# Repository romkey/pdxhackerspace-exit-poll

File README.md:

# PDX Hackerspace Exit Poll

Exit Poll is a display next to the door that shows, from Home Assistant,
whether anything in the space needs attention before the last person
leaves: open doors, unlocked doors, running water and AV equipment left on.
At PDX Hackerspace the last person out checks the space's physical security
and turns off equipment; member Kenny M had the idea of putting a dashboard by
the door so departing members can see at a glance whether anything needs
doing. The repo also holds a sibling project, an appliance countdown display
(washer, dryer, dishwasher, oven, 3D printer), built from the same parts.

> **AI disclosure:** This project was written by AI under human oversight,
> following [these rules](https://github.com/romkey/esphome-ai-coding-rules/blob/main/RULES.md).

## What's here

| Path | What it is |
|------|------------|
| [`packages/exit-poll.yaml`](packages/exit-poll.yaml) | Reads the 16 per-section counts from Home Assistant, totals them and publishes a System Status (0 good … 4 urgent) |
| [`packages/exit-poll-leds.yaml`](packages/exit-poll-leds.yaml) | LED strip showing the status as a color, with switches and buttons to override it |
| [`packages/exit-poll-lcars-320x480.yaml`](packages/exit-poll-lcars-320x480.yaml) | LCARS-style screen for a 320x480 SPI panel (mipi_spi) |
| [`packages/exit-poll-lvgl-480x800.yaml`](packages/exit-poll-lvgl-480x800.yaml) | LCARS-style LVGL screen for a 480x800 (portrait) panel |
| [`packages/appliances.yaml`](packages/appliances.yaml) | Reads appliance remaining-time sensors from Home Assistant |
| [`packages/appliances-grid-480x320.yaml`](packages/appliances-grid-480x320.yaml) | 3x2 grid of five appliances plus a clock, 480x320 SPI panel |
| [`packages/appliances-2-line-480x320.yaml`](packages/appliances-2-line-480x320.yaml) | Clock plus washer and dryer in two large rows, 480x320 SPI panel |
| `packages/assets/` | Fonts and LCARS images the display packages use |
| [`examples/tinys3.yaml`](examples/tinys3.yaml) | Exit Poll on a TinyS3 (ESP32-S3) and the Exit Poll PCB, ILI9488 panel |
| [`examples/hosyond-4in-cyd.yaml`](examples/hosyond-4in-cyd.yaml) | Exit Poll on a Hosyond 4" ESP32 display (ESP32, ST7796) |
| [`examples/guition-8048s550.yaml`](examples/guition-8048s550.yaml) | Exit Poll on a Guition 5" ESP32-S3 display, LVGL |
| [`examples/tinypico-appliances.yaml`](examples/tinypico-appliances.yaml) | Appliance grid on a TinyPICO (ESP32) |
| [`examples/hosyond-4in-cyd-appliances.yaml`](examples/hosyond-4in-cyd-appliances.yaml) | Two-line appliance display on the Hosyond 4" board |
| `examples/common/` | Settings shared by all examples, and the Hosyond board |
| [`docs/configuration.md`](docs/configuration.md) | Every package's requirements and substitutions |
| `pcb/` | KiCad files for the TinyS3 carrier PCB |
| `case/` | OpenSCAD and STL files for the 4" case |
| `lcars/` | Source art for the LCARS images |

The examples cover ESP32 and ESP32-S3. There is no ESP32-C3 example: none
of the boards this project runs on uses one.

## Technical details

### How it works

Home Assistant runs the space's security sensors. For each of four sections
of the space it provides four counts, `sensor.total_section_N_doors_open`,
`..._doors_unlocked`, `..._av_on` and `..._water_running`, which Exit Poll
mirrors (the entity ids are substitutions; see
[docs/configuration.md](docs/configuration.md)). The display shows each
count green when zero, red when not, gray when unknown. The LED strip shows
the worst state:

| Status | Meaning | LED color |
|--------|---------|-----------|
| 0 | All good | green |
| 1 | No Wi-Fi | orange |
| 2 | No Home Assistant connection | blue |
| 3 | AV on or water running | yellow |
| 4 | A door open or unlocked | red |

### Hardware

We use a cheap 320x480 SPI TFT display connected to Unexpected Maker's
[TinyS3](https://esp32s3.com/tinys3.html) on a custom PCB, but you can use
virtually any ESP32 board that's fast enough with enough storage and RAM
for your needs. We use displays with touch support - the PCB wires the touch
pins to the CPU but the SPI firmware doesn't use touch yet. The Hosyond and
Guition boards are all-in-one ESP32 displays that need no PCB.

If you want to use a different resolution display you'll need a new display
package.

TinyS3 + Exit Poll PCB wiring ([examples/tinys3.yaml](examples/tinys3.yaml)):

| Signal | GPIO |
|--------|------|
| SPI CLK | 9 |
| SPI MOSI | 36 |
| SPI MISO | 8 |
| Display CS | 2 |
| Display DC | 4 |
| Display reset | 3 |
| LED strip data | 7 |
| I2C SDA (Qwiic) | 21 |
| I2C SCL (Qwiic) | 5 |

The other boards' pins are in their examples, with links to the board
documentation they come from. There are no I2C devices on the SPI boards
(the bus goes to the Qwiic connector); the Guition board's GT911 touch
controller is at 0x5D.

The PCB is available at [OSHPark](https://oshpark.com/shared_projects/85wfS3FQ).

### Assembly

Most of the components on the board are optional.

C1 is entirely optional. It's intended to smooth power to the LED
strip, if you use one. In practice with just a few LEDs it's
unnecessary. We will probably drop it if we update the PCB again.

If you don't want the power indicator, omit D1 and R3.

If you don't want external I2C support via the Qwiic/Stemma QT
connector, omit R1, R2 and J3.

Although the board shows a female header strip for the connections on
the right hand side, ignore it if you're not using those for expansion
or wire them however is convenient for you if you are. You might for
instance wire in buttons for reset and programming (BOOT).

The bare minimum assembly is to solder the TinyS3 to the front of PCB
and then solder the display to the back. Be sure that the pinout of
the display you're using matches the pinout of the holes for its
pins. If it doesn't, you'll need to figure out how to wire it.

### Case

The repo includes [OpenSCAD files](https://openscad.org) for a minimal
case for a 4" display that mounts the display on a frame that snaps
into a box that can be mounted on a wall, with a hole in the bottom
for the USB power cable. If you use a different size display you will
need to redesign the case. It also includes the `.stl` files.

To print the case, load the `.stl` file into the slicer you use with
your 3D printer and follow your printer's instructions to slice and
print the case. PLA and PETG are good materials for the case.

## Building and using

Requires Docker.

```bash
cp examples/secrets.yaml.example examples/secrets.yaml   # then edit it
docker compose run --rm validate
docker compose run --rm build
docker compose run --rm lint
```

The first build downloads the toolchains into a Docker volume; later builds
reuse them and only recompile what changed. `docker compose up dashboard`
runs the ESPHome dashboard on http://localhost:6052.

For your own device, copy an example to `examples/local-<something>.yaml`
(gitignored) and override what you need; it can include the example and
change only a few substitutions:

```yaml
substitutions:
  name: exit-poll
  friendly_name: Exit Poll

packages:
  device: !include hosyond-4in-cyd.yaml
```

Flash it with `docker compose run --rm esphome run examples/local-<something>.yaml`.
Docker Desktop on macOS can't pass USB through: flash the first time with
https://web.esphome.io and use OTA after that.

### Using the packages from your own config

```yaml
substitutions:
  exit_poll_assets: assets   # a copy of packages/assets/ next to your config

packages:
  exit_poll: github://romkey/pdxhackerspace-exit-poll/packages/exit-poll.yaml@v0.4.0
  exit_poll_leds: github://romkey/pdxhackerspace-exit-poll/packages/exit-poll-leds.yaml@v0.4.0
  exit_poll_lcars: github://romkey/pdxhackerspace-exit-poll/packages/exit-poll-lcars-320x480.yaml@v0.4.0
```

ESPHome resolves font and image paths relative to your config, so copy
`packages/assets/` next to it. Your config must provide the ids and pins
each package lists in [docs/configuration.md](docs/configuration.md).

## License

[MIT](LICENSE)

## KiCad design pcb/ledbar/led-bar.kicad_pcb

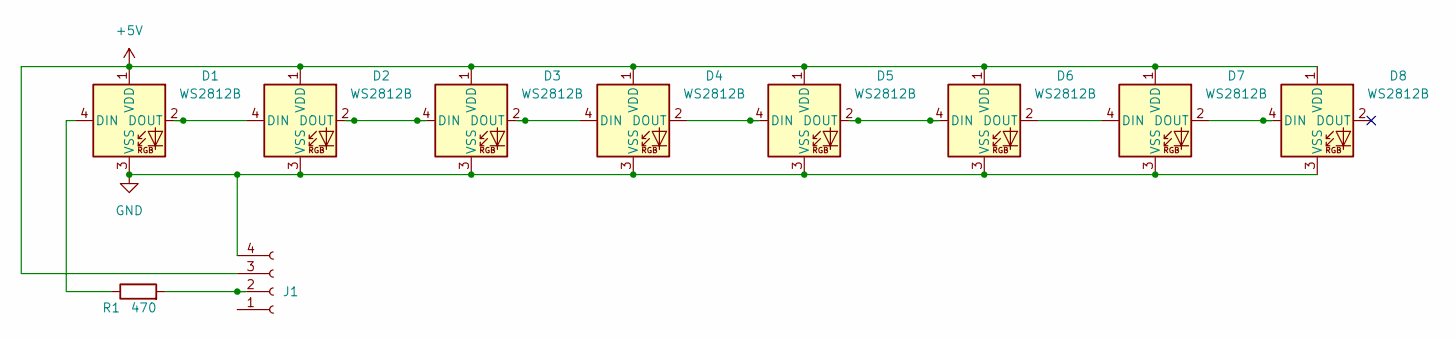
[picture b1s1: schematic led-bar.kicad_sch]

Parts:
D1, D2, D3, D4, D5, D6, D7, D8: WS2812B; LED-SMD_4P-L5.0-W5.0-TL_WS2812B-B; MPN C2761795
J1: Conn_01x04_Socket; CONN-TH_S4B-PH-KL-LF-SN; MPN C160235
R1: 470; R_1206_3216Metric_Pad1.30x1.75mm_HandSolder; MPN C140015

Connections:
+5V: D1.1 (VDD), D2.1 (VDD), D3.1 (VDD), D4.1 (VDD), D5.1 (VDD), D6.1 (VDD), D7.1 (VDD), D8.1 (VDD), J1.3
GND: D1.3 (VSS), D2.3 (VSS), D3.3 (VSS), D4.3 (VSS), D5.3 (VSS), D6.3 (VSS), D7.3 (VSS), D8.3 (VSS), J1.4
unnamed: D1.4 (DIN), R1.1
unnamed: D1.2 (DOUT), D2.4 (DIN)
unnamed: D2.2 (DOUT), D3.4 (DIN)
unnamed: D3.2 (DOUT), D4.4 (DIN)
unnamed: D4.2 (DOUT), D5.4 (DIN)
unnamed: D5.2 (DOUT), D6.4 (DIN)
unnamed: D6.2 (DOUT), D7.4 (DIN)
unnamed: D7.2 (DOUT), D8.4 (DIN)
unnamed: J1.2, R1.2

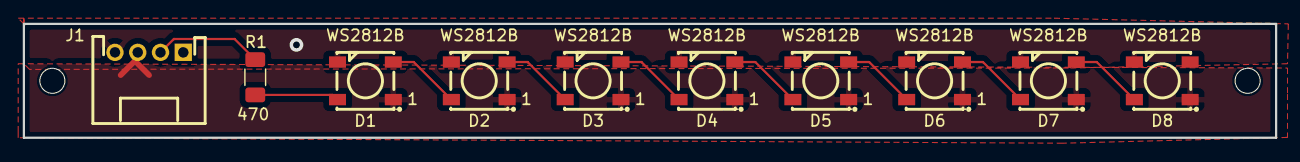
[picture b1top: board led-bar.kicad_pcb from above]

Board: 2 copper layers, 110.0 x 10.0 mm, 10 parts (0 on the bottom side), 11 nets.

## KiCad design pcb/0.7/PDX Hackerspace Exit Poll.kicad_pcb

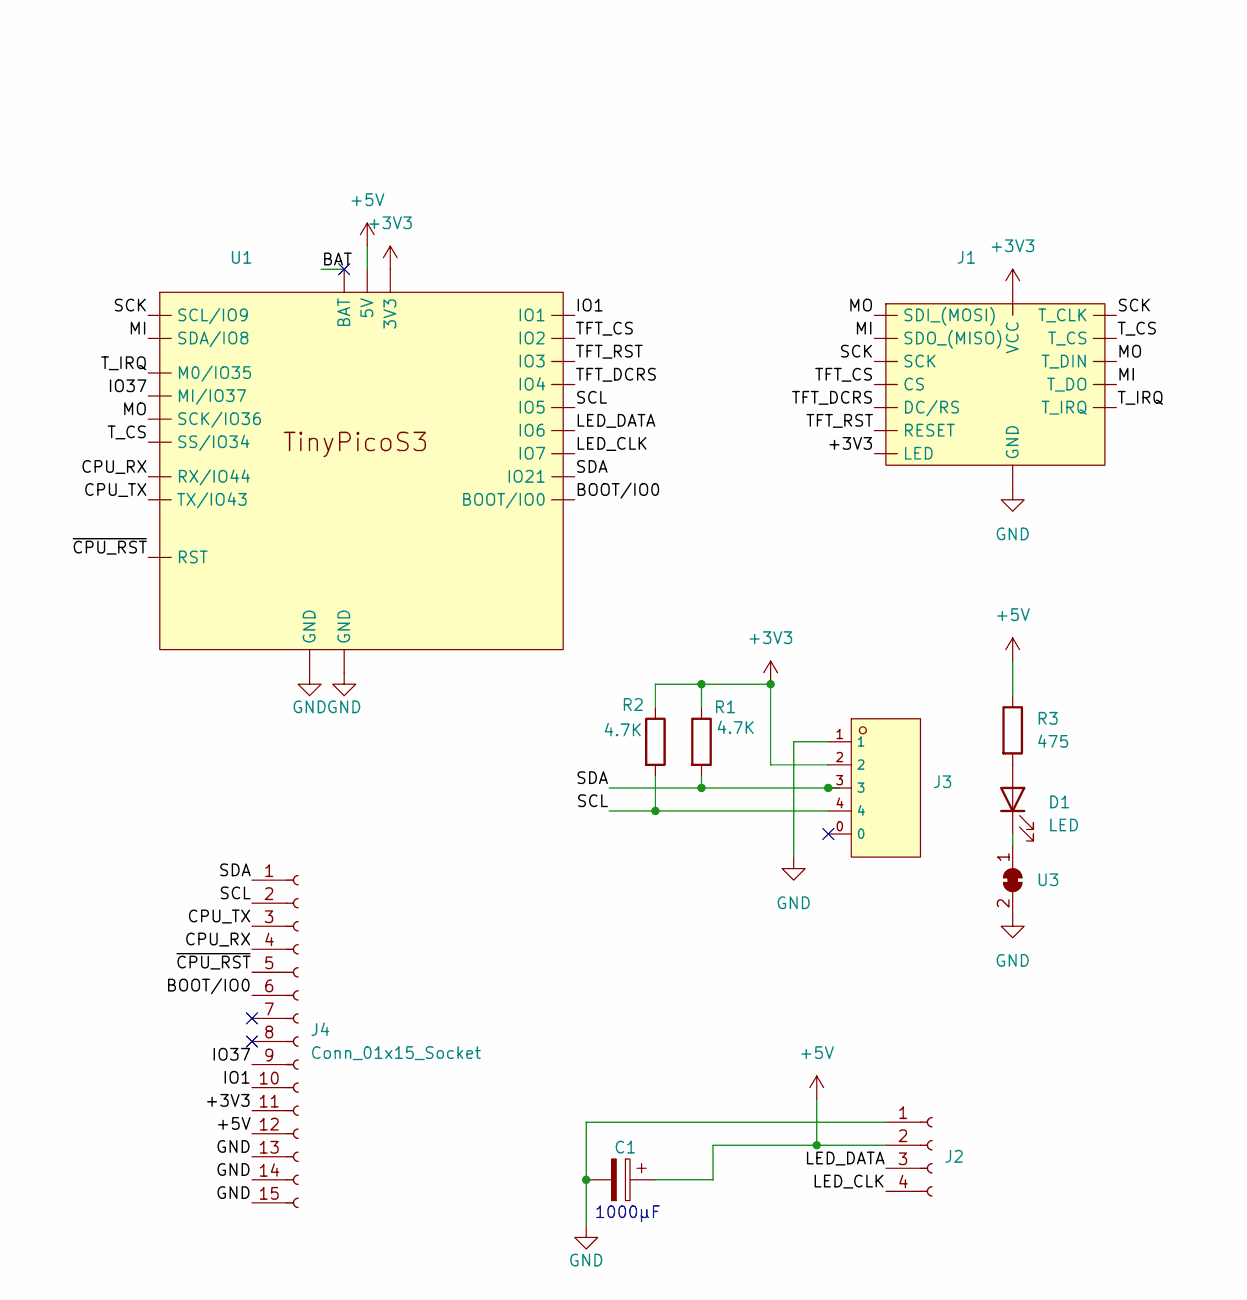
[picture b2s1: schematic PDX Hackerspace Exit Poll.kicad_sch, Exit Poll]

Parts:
C1: 100µF; CP_Elec_6.3x7.7; MPN C72477
D1: LED; LED_1206_3216Metric_Pad1.42x1.75mm_HandSolder; MPN C28310439
J1: SPI_TFT_TOUCH
J2: Conn_01x04_Socket; JST_PH_S4B-PH-K_1x04_P2.00mm_Horizontal; MPN C160235
J3: CONN-SMD_BM04B-SRSS-TB; MPN C160390; LCSC C160390
J4: Conn_01x15_Socket; PinSocket_1x15_P2.54mm_Vertical
R1, R2: 4.7K; R_0603_1608Metric_Pad0.98x0.95mm_HandSolder; MPN C4355002
R3: 475; R_1206_3216Metric_Pad1.30x1.75mm_HandSolder; MPN C323067
U1: TinyS3
U3: SolderJumper-2_P1.3mm_Bridged_RoundedPad1.0x1.5mm

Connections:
+3V3: J1.1 (VCC), J1.8 (LED), J3.2, J4.11, R1.1, R2.1, U1.20 (3V3)
+5V: C1.1, J2.2, J4.12, R3.1, U1.21 (5V)
/BAT: U1.23 (BAT)
/BOOT/IO0: J4.6, U1.13 (BOOT/IO0)
/CPU_RX: J4.4, U1.12 (RX/IO44)
/CPU_TX: J4.3, U1.11 (TX/IO43)
/IO1: J4.10, U1.19 (IO1)
/IO37: J4.9, U1.2 (MI/IO37)
/LED_CLK: J2.4, U1.7 (IO7)
/LED_DATA: J2.3, U1.8 (IO6)
/MI: J1.9 (SDO_(MISO)), J1.13 (T_DO), U1.6 (SDA/IO8)
/MO: J1.6 (SDI_(MOSI)), J1.12 (T_DIN), U1.3 (SCK/IO36)
/SCK: J1.7 (SCK), J1.10 (T_CLK), U1.5 (SCL/IO9)
/SCL: J3.4, J4.2, R2.2, U1.15 (IO5)
/SDA: J3.3, J4.1, R1.2, U1.14 (IO21)
/TFT_CS: J1.3 (CS), U1.18 (IO2)
/TFT_DCRS: J1.5 (DC/RS), U1.16 (IO4)
/TFT_RST: J1.4 (RESET), U1.17 (IO3)
/T_CS: J1.11 (T_CS), U1.4 (SS/IO34)
/T_IRQ: J1.14 (T_IRQ), U1.1 (M0/IO35)
/~CPU_RST: J4.5, U1.9 (RST)
GND: C1.2, J1.2 (GND), J2.1, J3.1, J4.13, J4.14, J4.15, U1.10 (GND), U1.22 (GND), U3.2 (B)
unnamed: D1.2 (A), R3.2
unnamed: D1.1 (K), U3.1 (A)

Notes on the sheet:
1000µF

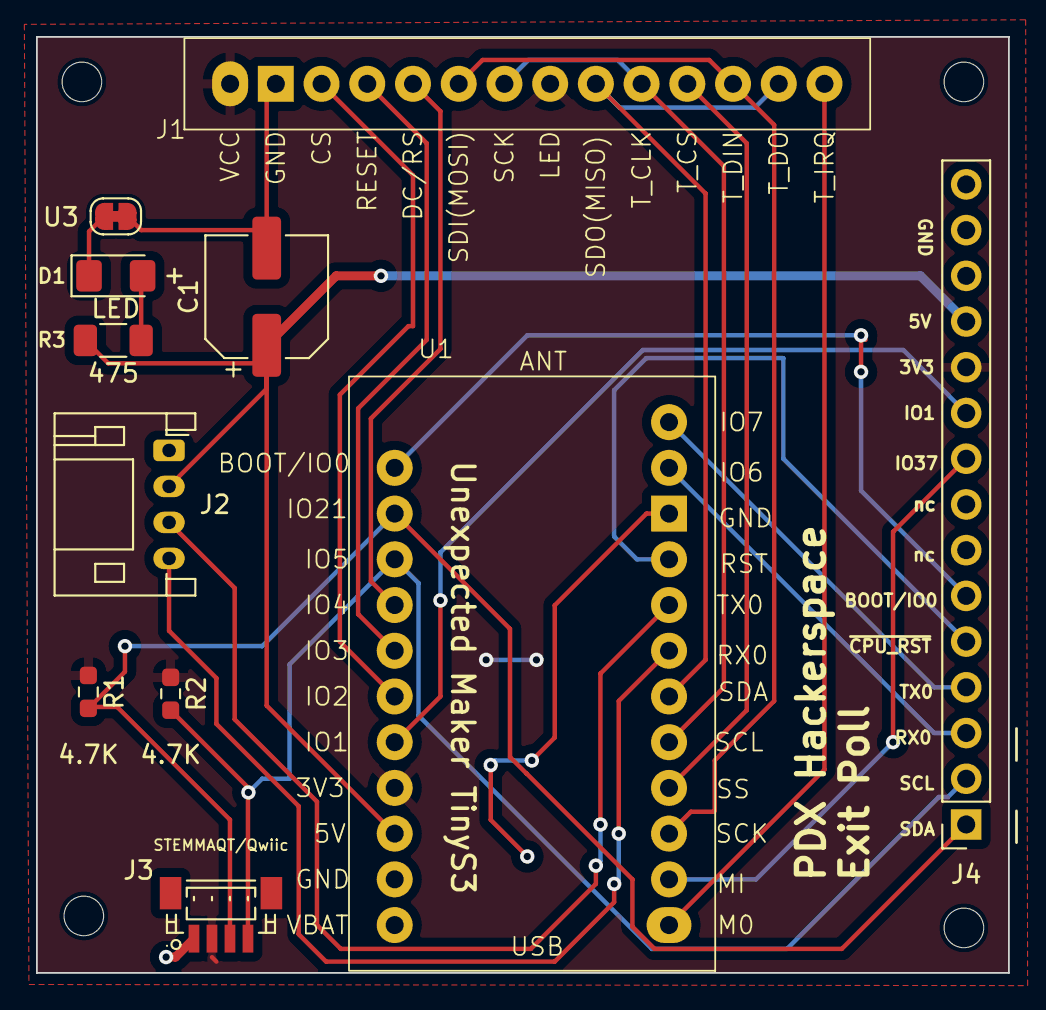
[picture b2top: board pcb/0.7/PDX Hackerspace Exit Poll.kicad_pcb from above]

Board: 2 copper layers, 54.0 x 52.0 mm, 12 parts (1 on the bottom side), 23 nets.

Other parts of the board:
G**: LOGO

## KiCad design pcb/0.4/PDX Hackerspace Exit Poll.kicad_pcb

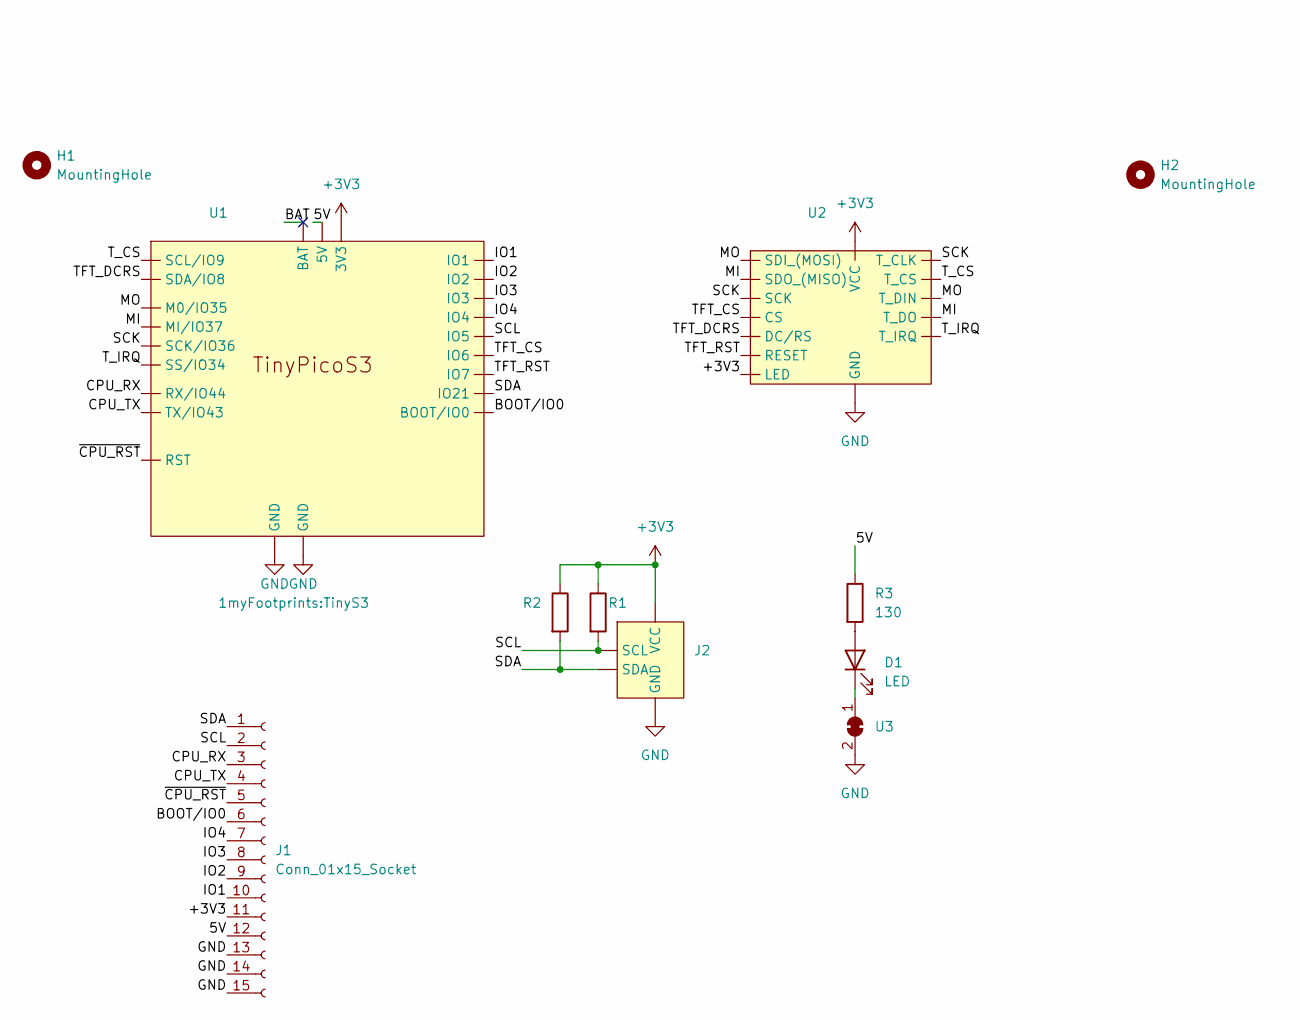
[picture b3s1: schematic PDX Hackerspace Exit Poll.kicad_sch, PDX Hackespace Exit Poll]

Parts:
D1: LED; LED_1206_3216Metric_Pad1.42x1.75mm_HandSolder
H1, H2: MountingHole; MountingHole_2.7mm_M2.5
J1: Conn_01x15_Socket; PinSocket_1x15_P2.54mm_Vertical
J2: JST_SH_SM04B-SRSS-TB_1x04-1MP_P1.00mm_Horizontal
R1, R2: 4.7K; R_Axial_DIN0204_L3.6mm_D1.6mm_P5.08mm_Horizontal
R3: 130; R_1206_3216Metric_Pad1.30x1.75mm_HandSolder
U1: TinyS3
U2: SPI_TFT_TOUCH
U3: SolderJumper-2_P1.3mm_Bridged_RoundedPad1.0x1.5mm

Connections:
+3V3: J1.11, J2.2 (VCC), R1.1, R2.1, U1.20 (3V3), U2.1 (VCC), U2.8 (LED)
/5V: J1.12, R3.1, U1.21 (5V)
/BAT: U1.23 (BAT)
/BOOT/IO0: J1.6, U1.13 (BOOT/IO0)
/CPU_RX: J1.3, U1.12 (RX/IO44)
/CPU_TX: J1.4, U1.11 (TX/IO43)
/IO1: J1.10, U1.19 (IO1)
/IO2: J1.9, U1.18 (IO2)
/IO3: J1.8, U1.17 (IO3)
/IO4: J1.7, U1.16 (IO4)
/MI: U1.2 (MI/IO37), U2.9 (SDO_(MISO)), U2.13 (T_DO)
/MO: U1.1 (M0/IO35), U2.6 (SDI_(MOSI)), U2.12 (T_DIN)
/SCK: U1.3 (SCK/IO36), U2.7 (SCK), U2.10 (T_CLK)
/SCL: J1.2, J2.4 (SCL), R1.2, U1.15 (IO5)
/SDA: J1.1, J2.3 (SDA), R2.2, U1.14 (IO21)
/TFT_CS: U1.8 (IO6), U2.3 (CS)
/TFT_DCRS: U1.6 (SDA/IO8), U2.5 (DC/RS)
/TFT_RST: U1.7 (IO7), U2.4 (RESET)
/T_CS: U1.5 (SCL/IO9), U2.11 (T_CS)
/T_IRQ: U1.4 (SS/IO34), U2.14 (T_IRQ)
/~CPU_RST: J1.5, U1.9 (RST)
GND: J1.13, J1.14, J1.15, J2.1 (GND), U1.10 (GND), U1.22 (GND), U2.2 (GND), U3.2 (B)
unnamed: D1.2 (A), R3.2
unnamed: D1.1 (K), U3.1 (A)

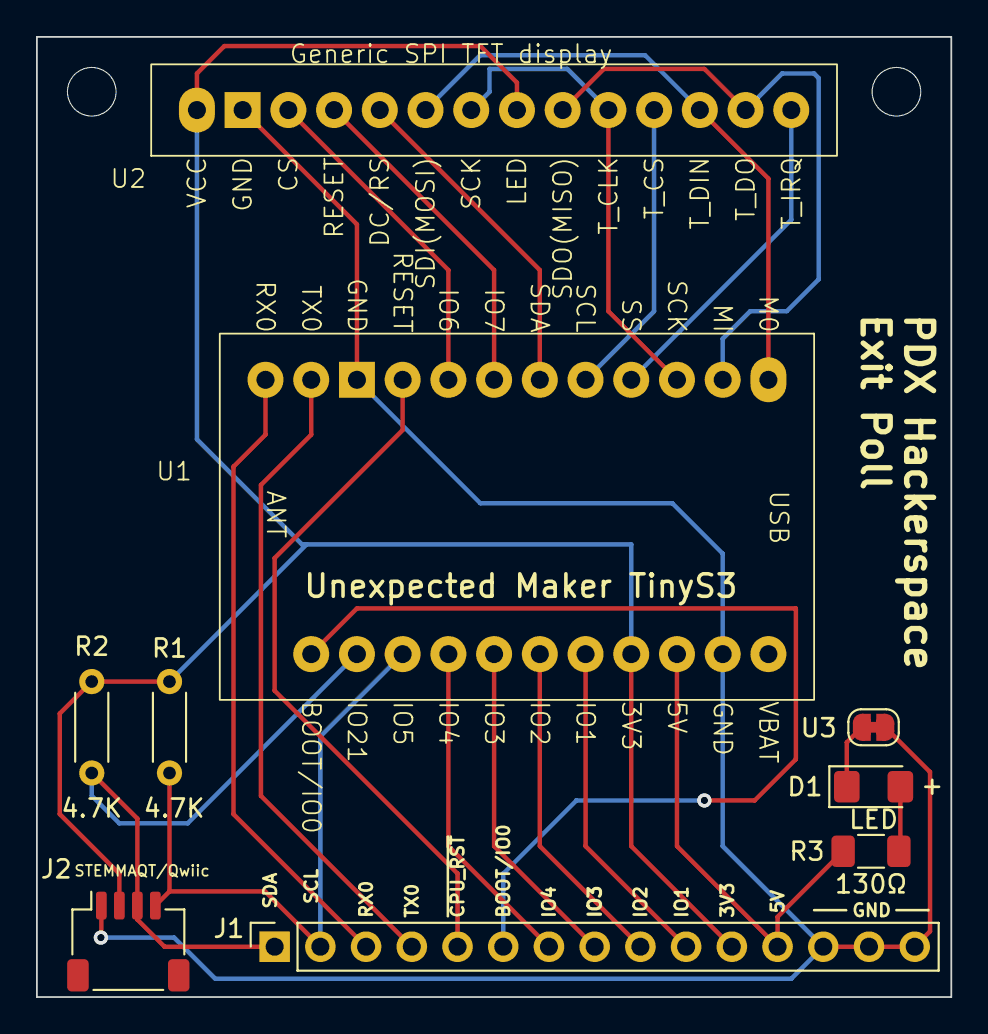
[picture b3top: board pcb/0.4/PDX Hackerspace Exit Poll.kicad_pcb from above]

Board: 2 copper layers, 50.8 x 53.3 mm, 11 parts (0 on the bottom side), 23 nets.

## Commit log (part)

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2024-07-20 added MIT license and Adafruit code of conduct
2024-12-08 split out essential functionality to be included as packages
2024-12-08 helps to spell "substitutions" correctly
2024-12-08 try quotes
2024-12-08 KiCAD and image files for 0.7 pcb
2024-12-08 fixed a couple of substitution names
2024-12-08 updated example top level ESPHome file
2024-12-08 moved led_number out of tinys3.yml
    updated README
2024-12-08 updated README
    added preview of case as well as updated OpenSCAD file
2024-12-08 comment on C1
2024-12-09 finally include images of the actual device
2024-12-09 make photos smaller
2024-12-09 smaller still
2024-12-30 Starting to notate the scad file for easier feature detection
2024-12-30 Added slot to protect touchscreen pins, exported model for print test
2024-12-30 exported the wrong model, oops!
2024-12-31 Added a small cutout on the front cover to keep the display cable from getting smushed
